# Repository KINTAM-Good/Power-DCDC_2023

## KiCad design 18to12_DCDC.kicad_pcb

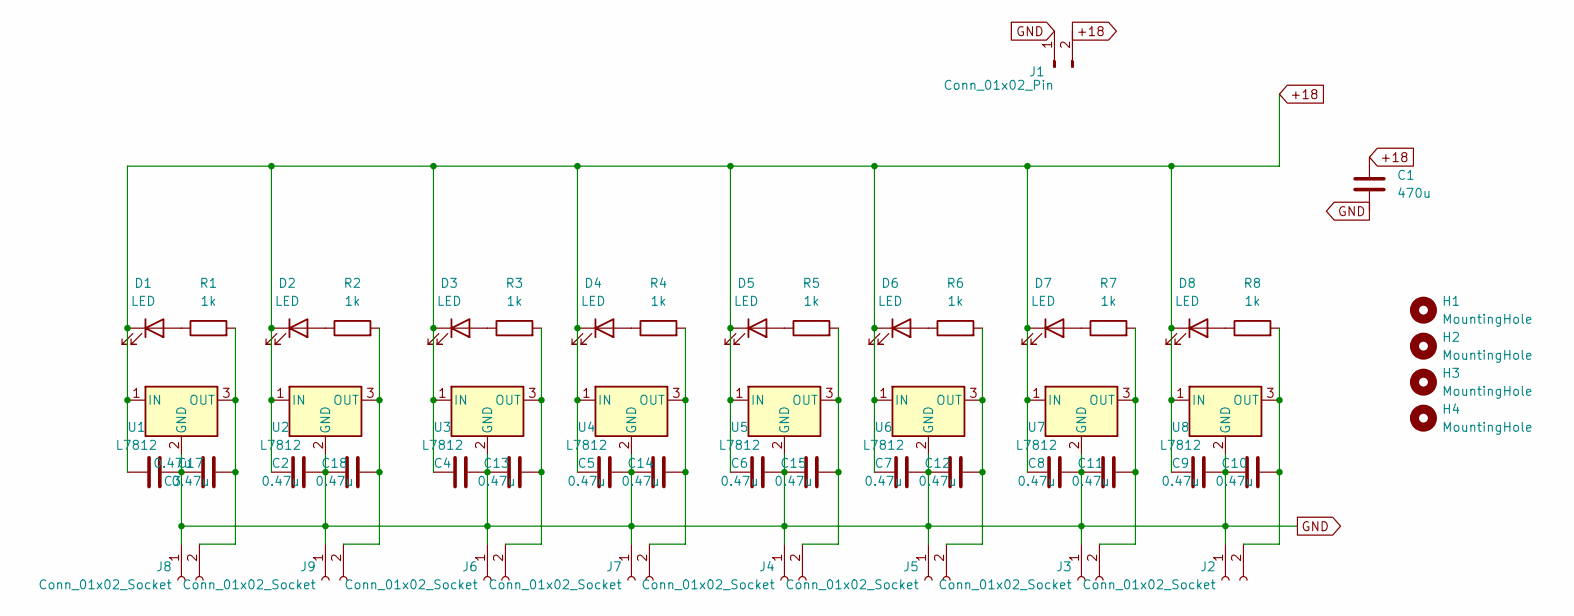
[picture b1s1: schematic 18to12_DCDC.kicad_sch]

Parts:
C1: 470u; CP_Radial_D13.0mm_P5.00mm
C2, C3, C4, C5, C6, C7, C8, C9, C10, C11, C12, C13, C14, C15, C17, C18: 0.47u; via_2
D1, D2, D3, D4, D5, D6, D7, D8: LED; LED_0603_1608Metric
H1, H2, H3, H4: MountingHole; MountingHole_3.2mm_M3_Pad_Via
J1: Conn_01x02_Pin; AMASS_XT60-F_1x02_P7.20mm_Vertical
J2, J3, J4, J5, J6: Conn_01x02_Socket; AMASS_XT60-F_1x02_P7.20mm_Vertical
J7, J8, J9: Conn_01x02_Socket; JST_XH_S2B-XH-A_1x02_P2.50mm_Horizontal
R1, R2, R3, R4, R5, R6, R7, R8: 1k; R_0603_1608Metric
U1, U2, U3, U4, U5, U6, U7, U8: L7812; TO-252-2

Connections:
+18: C1.1, C2.1, C3.2, C4.1, C5.1, C6.1, C7.1, C8.1, C9.1, D1.1 (K), D2.1 (K), D3.1 (K), D4.1 (K), D5.1 (K), D6.1 (K), D7.1 (K), D8.1 (K), J1.2, U1.1 (IN), U2.1 (IN), U3.1 (IN), U4.1 (IN), U5.1 (IN), U6.1 (IN), U7.1 (IN), U8.1 (IN)
GND: C1.2, C2.2, C3.1, C4.2, C5.2, C6.2, C7.2, C8.2, C9.2, C10.1, C11.1, C12.1, C13.1, C14.1, C15.1, C17.1, C18.1, J1.1, J2.1, J3.1, J4.1, J5.1, J6.1, J7.1, J8.1, J9.1, U1.2 (GND), U2.2 (GND), U3.2 (GND), U4.2 (GND), U5.2 (GND), U6.2 (GND), U7.2 (GND), U8.2 (GND)
unnamed: D1.2 (A), R1.1
unnamed: D2.2 (A), R2.1
unnamed: D3.2 (A), R3.1
unnamed: D4.2 (A), R4.1
unnamed: D5.2 (A), R5.1
unnamed: D6.2 (A), R6.1
unnamed: D7.2 (A), R7.1
unnamed: D8.2 (A), R8.1
unnamed: C10.2, J2.2, R8.2, U8.3 (OUT)
unnamed: C11.2, J3.2, R7.2, U7.3 (OUT)
unnamed: C15.2, J4.2, R5.2, U5.3 (OUT)
unnamed: C12.2, J5.2, R6.2, U6.3 (OUT)
unnamed: C13.2, J6.2, R3.2, U3.3 (OUT)
unnamed: C14.2, J7.2, R4.2, U4.3 (OUT)
unnamed: C17.2, J8.2, R1.2, U1.3 (OUT)
unnamed: C18.2, J9.2, R2.2, U2.3 (OUT)

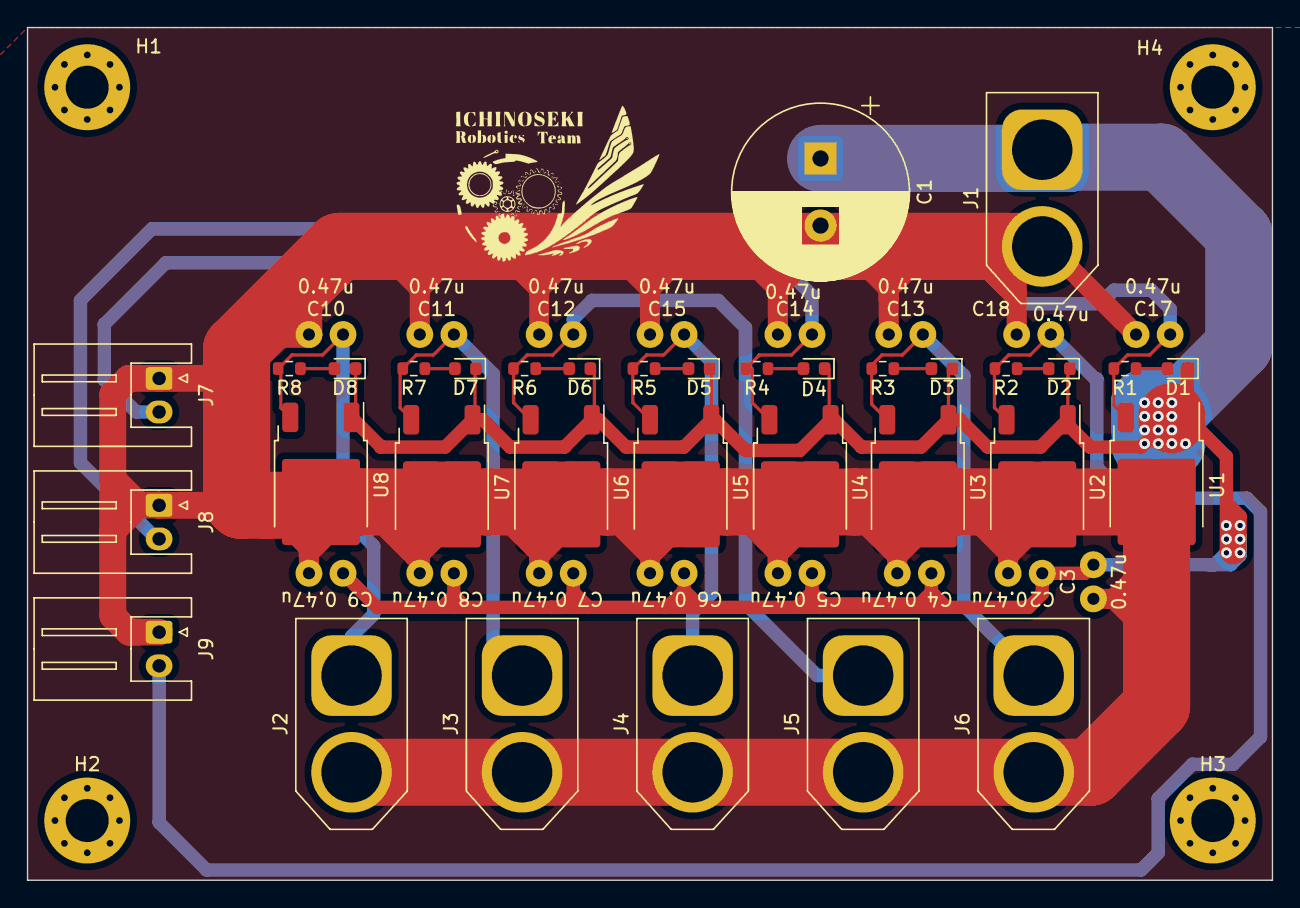
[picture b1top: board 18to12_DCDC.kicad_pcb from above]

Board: 2 copper layers, 92.7 x 63.5 mm, 55 parts (0 on the bottom side), 18 nets.

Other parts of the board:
J8#2: Logo; INCT
